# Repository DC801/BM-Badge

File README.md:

# DC801 Black Mage Badge

The DC801 Badge Platform for DC28+, featuring a [playable web build](https://dc801.github.io/BM-Badge/) to increase ease of access for content authorship workflows, as well as for archival access to the game when for the hardware is no longer available.

## Introducing Chapter 2 (for DC32)

A new expansion for the game has been added! Chapter 2 introduces King Gibson's castle and the badge's built-in USB-C serial interface. More characters, more puzzles, and more puns!

Use the terminal to engage with the world and solve puzzles:

Chapter 1 content is still available with this release, and both chapters are accessible from the main menu.

## Videos about the project

<a href="https://www.youtube.com/watch?v=QbsCsldlNKE" target="_blank">
<br />Watch Alex Chaveriat's review of the DC801 Black Mage Badge</a>

----

<a href="https://www.youtube.com/watch?v=-YtiRvzJ-uo" target="_blank">
<br />Watch Alex Chaveriat interview Hamster at DEFCON 29 about the DC801 Black Mage Badge</a>

----

<a href="https://www.youtube.com/watch?v=cmqgIxQA0Sg" target="_blank">
<br />Watch Alex Chaveriat interview Admiral Potato and Alamedyang about building the DC801 Black Mage Badge</a>

## Hardware

The DC801 BM-Badge brings you an expandable iteration of our robust platfom.

 - Core CPU is the Nordic nRF52840 SoC, on the u-blox BMD-340 module
   - [https://www.u-blox.com/en/product/bmd-34-series-open-cpu](https://www.u-blox.com/en/product/bmd-34-series-open-cpu)
   - 256k RAM, 1M internal flash, ARM® Cortex™ M4F CP @ 64Mhz
   - Bluetooth 5 with Bluetooth mesh and Zigbee support
   - Temperature sensor
 - 27 buttons with NKRO via a dedicated controller
   - Microchip ATiny1617 microcontroller, with UPDI programming support
   - [https://www.microchip.com/wwwproducts/en/ATtiny1617](https://www.microchip.com/wwwproducts/en/ATtiny1617)
 - 19 LEDs
 - SD card socket
 - 32MB of quad-spi flash
 - NAU8810 audio codec and speaker
 - 2.4" 240x320 TFT LCD screen with touch panel
 - LiPo battery with on-board charging
 - USB-C interface supporting USB endpoints
 - SAO 1.69bis and Saintcon MiniBadge expansion headers
 - Support for the DC801 ART front board expansion
 - JTAG via both standard ARM interface as well as Tag Connect
 - USB drag-and-drop programming via a UF2 interface (based on the [adafruit bootloader](https://github.com/adafruit/Adafruit_nRF52_Bootloader))
 - Exciting new artwork and sandwich design

Board design is in KiCad

See the [HW](/HW) directory for more info, schematics and etc

### ART - Asymmetric Resistive Token
Since this badge is a sandwich platform badge, we've include a template so that you can design your own front boards.

Check out the [Template](/HW/ART/Template) that you can create a new project in KiCad with.

## Software
 - Environment is GNU ARM GCC with your choice of IDE (We're currently using CLion and VSCode)
 - Need a J-Link Segger JTAG programmer to program the chip directly.
 - Custom game engine purpose-built for the badge that can automatically load custom games from the SD Card.
 - Included in the [SD_Card/MAGE](/SD_Card/MAGE) directory is a binary encoder that allows you to generate your own games with our engine using open source tools such as the Tiled Map Editor and our custom json scripting language.
 - Instructions to set up your own dev environment and desktop testing build of our game engine in [EnvironmentSetup.md](/EnvironmentSetup).
 - [Comprehensive engine documentation and content creation guide](SD_Card/MAGE/README.md)

## Gameplay Videos

[DC28 DC801 SAFEMODE badge, 2020-12-04 development update](https://vimeo.com/487527877): Watch almost 6 minutes of 100% in-engine gameplay in our 2020-12-04 development update video!

[DC28 DC801 SAFEMODE badge, 2021-02-21 development update](https://vimeo.com/515088170):
Watch one of our puzzles and see some of our new narrative focused engine scripting capabilities in our 2021-02-21 development update video!

----

## DC32 dev team

### Hardware

#### PCB Electronics
- @hamster

#### PCB Art
- corfidbizna
- alamedyang

#### Badge Design
- @admiral_potato
- @hamster

#### Art Board
- redactd

#### Joystick Covers
- @_Pexie

#### Software

#### Engine Lead
- @admiral_potato

#### Script System
- @admiral_potato

#### Script Tooling
- alamedyang
- @admiral_potato
- nibley

#### Programming Support
- Tawnos
- Solra Bizna
- Youssef Moosa
- Cedric Hutchings (cedric_h)

### Graphics

#### 2D Art
- alamedyang
- corfidbizna
- Hippi3Hack3r

#### 3D Art
- @admiral_potato
- nthday

### Story

#### Writing
- alamedyang
- Hippi3Hack3r

#### Scripting
- alamedyang
- ThatDeadGuy and CJDJ
- nibley
- mmedei
- korinakuma

#### Goose Facts Consultant
- lys

### Special Thanks
- 7thdrxn
- Aaron Freed
- anonbecause
- courtyen
- DisplayGFX
- flame3722
- HeyItsWaters
- hipu
- HumanDLC
- korinakuma
- laughdat
- Liam "junkmail" Thomas
- @MuxLuxx
- NewGnu
- @_Pexie
- Solra Bizna
- Spooks
- TuckleberryWinn
- And all the playtesters who we missed!

----

## DC28 dev team

Project owner
- [@nemus](https://twitter.com/Nemus801)

Software Team
- [@_bashNinja](https://twitter.com/_bashNinja)
- [@admiral_potato](https://twitter.com/admiral_potato)
- [@corfidbizna](https://twitter.com/corfidbizna)
- [kiyoshigawa](https://twa.ninja/)
- [@newzie1](https://twitter.com/newzie1)
- [@tazmodius](https://twitter.com/tazmodius)
- @alamedyang

Hardware Team
- [@dvdfreitag](https://twitter.com/dvdfreitag)
- [@hamster](https://twitter.com/hamster)

Honorable Mention
- [@pips801](https://twitter.com/pips801)

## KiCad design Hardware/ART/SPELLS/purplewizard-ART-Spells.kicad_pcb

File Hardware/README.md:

We will provide the hardware schematics and KiCAD files once we ship the final badge designs.

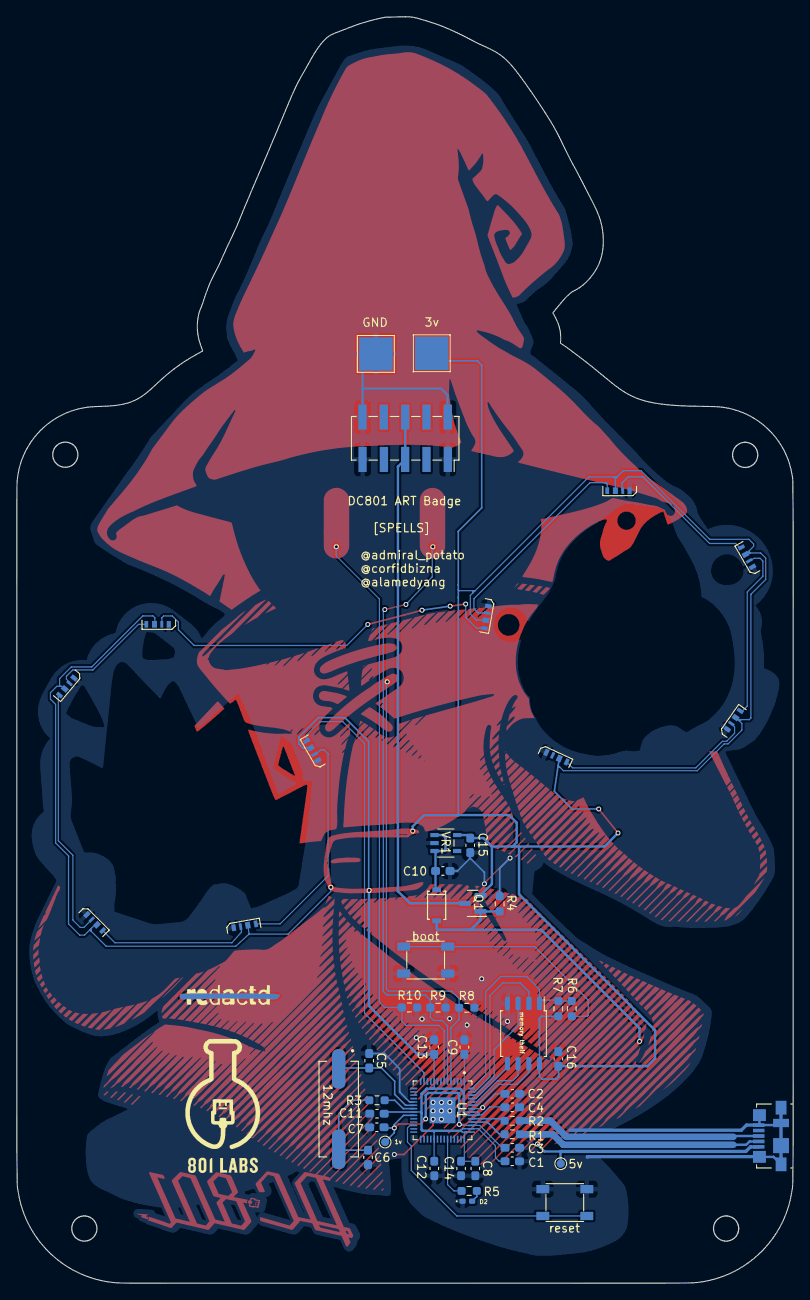
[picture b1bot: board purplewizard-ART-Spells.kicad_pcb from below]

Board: 2 copper layers, 92.5 x 151.0 mm, 52 parts (52 on the bottom side), 36 nets.

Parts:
1v: 1v; TestPoint_Pad_D1.0mm
3v: 3v3; TestPoint_Pad_4.0x4.0mm
5v: 5v; TestPoint_Pad_D1.0mm
12mhz: ABLS-12.000MHZ-B4-T; XTAL1140X470X420N
C1, C10, C15: 1uF; C_0603_1608Metric_Pad1.08x0.95mm_HandSolder
C2, C4, C7, C8, C9, C11, C12, C13, C14, C16: 100n; C_0603_1608Metric_Pad1.08x0.95mm_HandSolder
C3: 1u; C_0603_1608Metric_Pad1.08x0.95mm_HandSolder
C5, C6: 27pF; C_0603_1608Metric_Pad1.08x0.95mm_HandSolder
D1: D_Schottky; SM5819PL-TP
D2: LED; LED_0402_1005Metric_Pad0.77x0.64mm_HandSolder
D3, D4, D5, D6, D7, D8, D9, D10, D11, D12: LED_SK6812_4020_SIDE
GND: GND; TestPoint_Pad_4.0x4.0mm
J1: ART Expansion; PinSocket_2x05_P2.54mm_Vertical_SMD
J4: USB_B_Micro; USB_Micro-B_Molex_47346-0001
Q1: DMG2301L; SOT-23
R1, R2: 27; R_0603_1608Metric_Pad0.98x0.95mm_HandSolder
R3, R5, R6: 1k; R_0603_1608Metric_Pad0.98x0.95mm_HandSolder
R4, R7: 10k; R_0603_1608Metric_Pad0.98x0.95mm_HandSolder
R8, R9, R10: 1M; R_0603_1608Metric_Pad0.98x0.95mm_HandSolder
Ref**: Val**; redactd_copper_strike_v1
U1: RP2040; QFN40P700X700X90-57N
VR1: AP7366-33W5-7; AP7365-33WG-7
boot: SW_SPST; SW_SPST_PTS647
memory theif: W25Q32JVSS; SOIC-8_5.23x5.23mm_P1.27mm
reset: SW_SPST_PTS647

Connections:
+1V1: 1v.1, C2.1, C3.2, C7.1, U1.23 (DVDD), U1.45 (VREG_VOUT), U1.50 (DVDD)
+3.3VP: J1.5, J1.6, Q1.3 (D)
+3V3: 3v.1, C1.2, C4.1, C8.1, C9.1, C11.1, C12.1, C13.1, C14.1, C15.1, C16.1, D3.2 (VDD), D4.2 (VDD), D5.2 (VDD), D6.2 (VDD), D7.2 (VDD), D8.2 (VDD), D9.2 (VDD), D10.2 (VDD), D11.2 (VDD), D12.2 (VDD), Q1.2 (S), R7.1, U1.1 (IOVDD), U1.10 (IOVDD), U1.22 (IOVDD), U1.33 (IOVDD), U1.42 (IOVDD), U1.43 (ADC_AVDD), U1.44 (VREG_VIN), U1.48 (USB_VDD), U1.49 (IOVDD), VR1.5 (OUT), memory theif.8 (VCC)
D+: J4.3 (D+), R2.2
D-: J4.2 (D-), R1.2
GND: C1.1, C2.2, C3.1, C4.2, C5.1, C6.1, C7.2, C8.2, C9.2, C10.2, C11.2, C12.2, C13.2, C14.2, C15.2, C16.2, D2.1 (K), D3.4 (GND), D4.4 (GND), D5.4 (GND), D6.4 (GND), D7.4 (GND), D8.4 (GND), D9.4 (GND), D10.4 (GND), D11.4 (GND), D12.4 (GND), GND.1, J1.1, J1.2, J1.9, J1.10, J4.5 (GND), J4.6 (Shield), R4.2, R8.2, R9.2, R10.2, U1.19 (TESTEN), U1.57 (GND), VR1.2 (GND), boot.2 (B), memory theif.4 (GND), reset.2 (B)
GPIO25: R5.1, U1.37 (GPIO25)
NEO: D3.1 (DIN), U1.13 (GPIO10)
unnamed: 12mhz.2, C6.2, R3.2
unnamed: C10.1, D1.1 (K), VR1.1 (IN), VR1.3 (EN)
unnamed: D2.2 (A), R5.2
unnamed: D3.3 (DOUT), D4.1 (DIN)
unnamed: D4.3 (DOUT), D5.1 (DIN)
unnamed: D5.3 (DOUT), D6.1 (DIN)
unnamed: D6.3 (DOUT), D7.1 (DIN)
unnamed: D7.3 (DOUT), D8.1 (DIN)
unnamed: D8.3 (DOUT), D9.1 (DIN)
unnamed: D9.3 (DOUT), D10.1 (DIN)
unnamed: D10.3 (DOUT), D11.1 (DIN)
unnamed: D11.3 (DOUT), D12.1 (DIN)
unnamed: R1.1, U1.46 (USB_DM)
unnamed: R2.1, U1.47 (USB_DP)
QSPI_SCLK: U1.52 (QSPI_SCLK), memory theif.6 (CLK)
QSPI_SD0: U1.53 (QSPI_SD0), memory theif.5 (DI(IO0))
QSPI_SD1: U1.55 (QSPI_SD1), memory theif.2 (DO(IO1))
QSPI_SD2: U1.54 (QSPI_SD2), memory theif.3 (IO2)
QSPI_SD3: U1.51 (QSPI_SD3), memory theif.7 (IO3)
QSPI_SS: R6.1, R7.2, U1.56 (QSPI_CSN), memory theif.1 (~CS)
RUN: U1.26 (RUN), reset.1 (A)
TOUCH1: R8.1, U1.5 (GPIO3)
TOUCH2: R9.1, U1.6 (GPIO4)
TOUCH3: R10.1, U1.7 (GPIO5)
USB_BOOT: R6.2, boot.1 (A)
VBUS: 5v.1, D1.2 (A), J4.1 (VBUS), Q1.1 (G), R4.1
XIN: 12mhz.1, C5.2, U1.20 (XIN)
XOUT: R3.1, U1.21 (XOUT)

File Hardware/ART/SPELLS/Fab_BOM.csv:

,,,,,,,
,,,,,,,
,,,,,,,
,,Reference,Value,Package,Source,Datasheet,Quantity
,,"C2, C4, C7, C8, C9, C11, C12, C13, C14, C16",100n,0603,~,,10
,,"C1, C3, C10, C15",1u,0603,~,,4
,,"C5, C6",1pF,0603,~,,2
,,"R8, R9, R10",1M,0603,~,,3
,,"R1, R2",27,0603,~,,2
,,"R4, R7",10k,0603,~,,2
,,"R3, R5, R6",1k,0603,~,,3
,,"D3, D4, D5, D6, D7, D8, D9, D10, D11, D12",SK6812SIDE-A,,https://www.lcsc.com/product-detail/Light-Emitting-Diodes-LE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,~,10
,,D1,Schottky,SOD-123,https://www.digikey.com/en/products/detail/micro-commercial-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,,1
,,D2,Red,0402,https://www.lcsc.com/product-detail/Light-Emitting-Diodes-sp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,,1
,,Q1,DMG2301L,SOT-23,https://www.digikey.com/en/products/detail/diodes-incorporat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,,1
,,U1,RP2040,QFN56,https://www.lcsc.com/product-detail/Microcontroller-Units-MC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,,1
,,U2,W25Q32JVSS,SOIC-8,https://www.lcsc.com/product-detail/NOR-FLASH_Winbond-Elec-W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,,1
,,Y1,ABLS-12.000MHZ-B4-T,,https://www.digikey.com/en/products/detail/abracon-llc/ABLS-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,~,1
,,"SW1, SW2",SPST,,https://www.lcsc.com/product-detail/Tactile-Switches_TE-Conn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,,2
,,J1,2x5 2.54 SMD,,https://www.digikey.com/en/products/detail/amphenol-cs-fci/1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,,1
,,J4,USB Micro Molex,,https://www.digikey.com/en/products/detail/molex/0473460001/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,,1
,,VR1,AP7366-33W5-7,SOT-25,https://www.lcsc.com/product-detail/Linear-Voltage-Regulator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,~,1

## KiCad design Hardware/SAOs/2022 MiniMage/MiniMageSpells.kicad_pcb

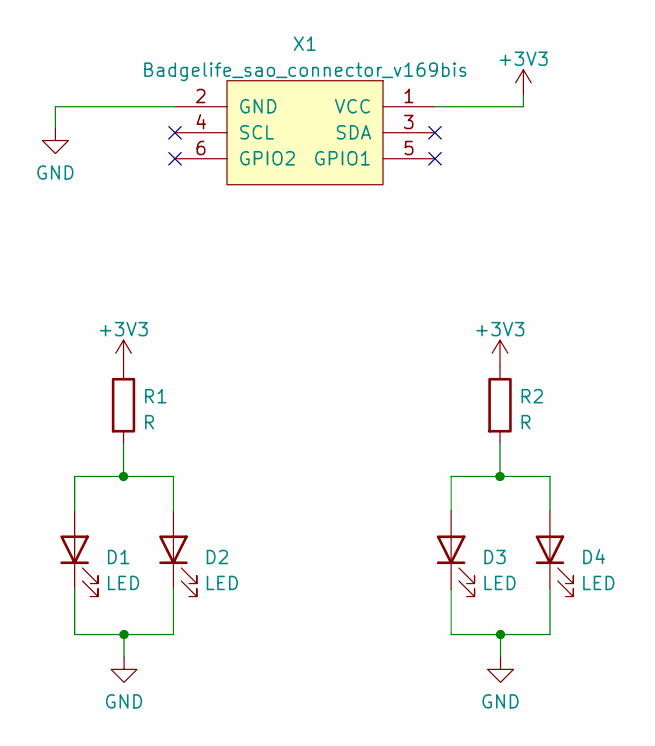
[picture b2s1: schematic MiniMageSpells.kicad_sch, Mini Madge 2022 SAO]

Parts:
D1, D2, D3, D4: LED; LED_0805_2012Metric
R1, R2: R; R_0805_2012Metric
X1: Badgelife_sao_connector_v169bis; PinHeader_2x03_P2.54mm_Vertical_SMD

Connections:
+3V3: R1.1, R2.1, X1.1 (VCC)
GND: D1.1 (K), D2.1 (K), D3.1 (K), D4.1 (K), X1.2 (GND)
unnamed: D1.2 (A), D2.2 (A), R1.2
unnamed: D3.2 (A), D4.2 (A), R2.2

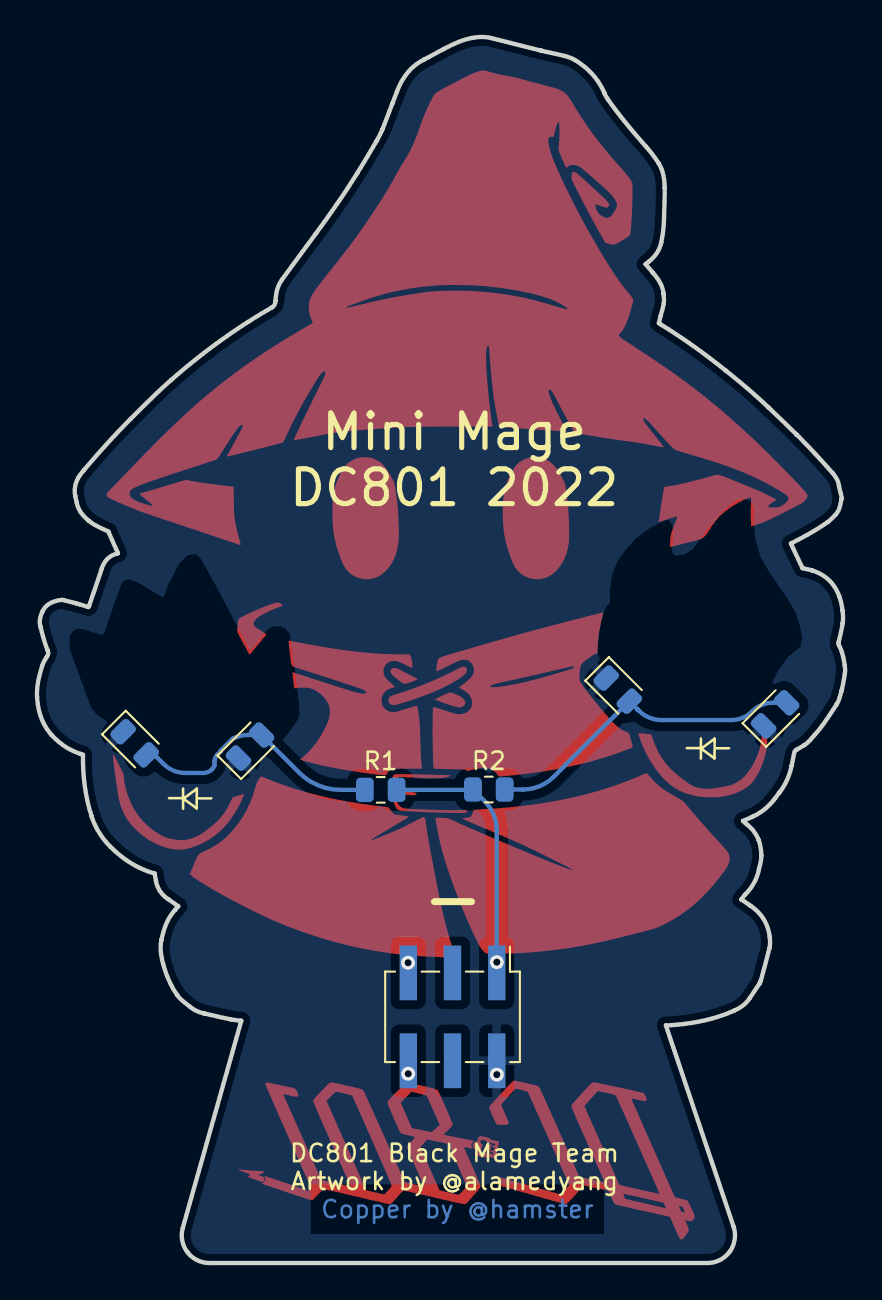
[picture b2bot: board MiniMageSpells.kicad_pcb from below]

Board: 2 copper layers, 46.4 x 70.4 mm, 7 parts (7 on the bottom side), 4 nets.

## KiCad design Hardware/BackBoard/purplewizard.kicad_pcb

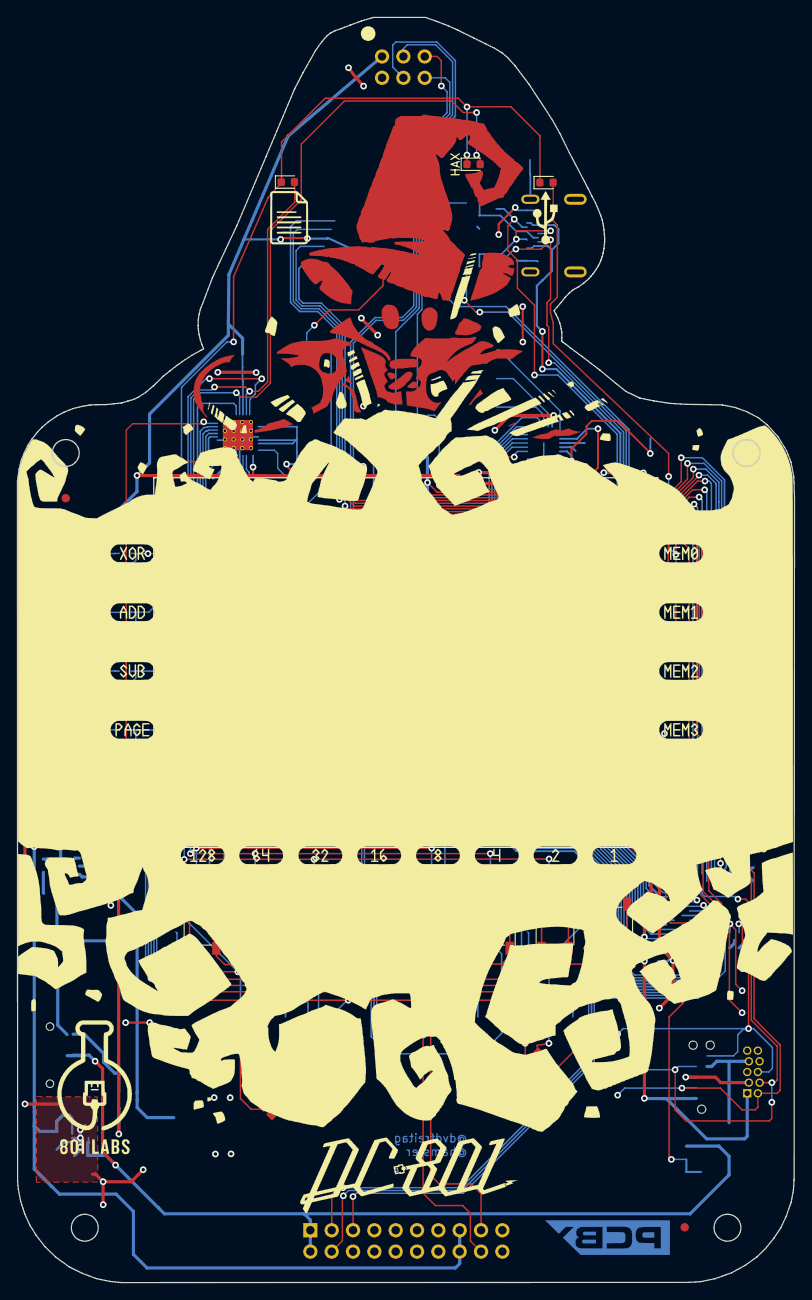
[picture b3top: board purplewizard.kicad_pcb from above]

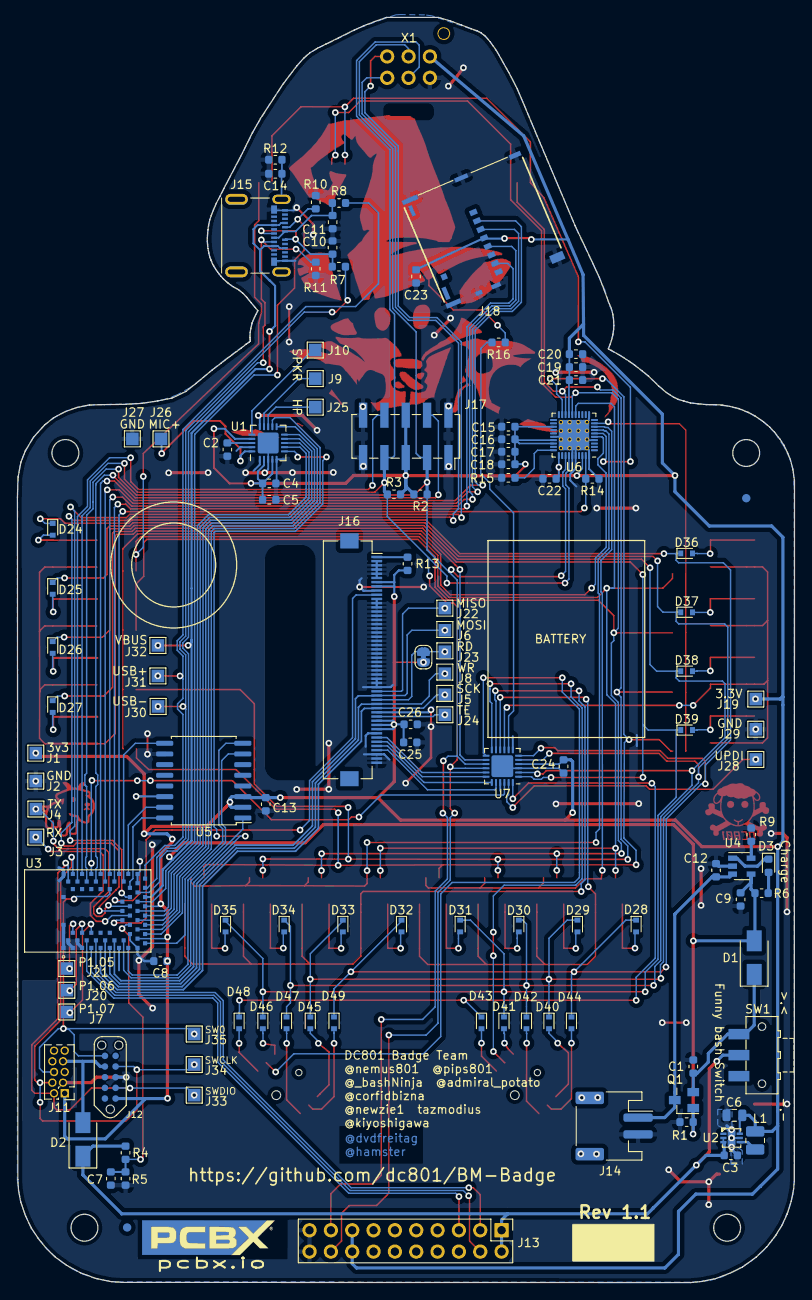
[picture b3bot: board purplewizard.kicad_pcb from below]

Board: 2 copper layers, 92.5 x 150.6 mm, 159 parts (118 on the bottom side), 121 nets.

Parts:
C1, C13, C14, C15, C17, C20, C23, C24, C25: 0.1uF; C_0603_1608Metric
C2, C4, C5, C8, C9, C12: 4.7uF; C_0603_1608Metric
C3, C26: 10uF; C_0603_1608Metric
C6: 22uF; C_0805_2012Metric
C7: 1nF; C_0603_1608Metric
C10, C11: 47pF; C_0603_1608Metric
C16, C18, C21, C22: 0.47uF; C_0603_1608Metric
C19: 22uF; C_0603_1608Metric
D1, D2: D_Schottky; D_SMA
D3: RED; LED_0603_1608Metric
D5: XOR; LED_0603_1608Metric
D6: MEM0; LED_0603_1608Metric
D7: BIT128; LED_0603_1608Metric
D8: BIT8; LED_0603_1608Metric
D9: USB; LED_0603_1608Metric
D10: ADD; LED_0603_1608Metric
D11: MEM1; LED_0603_1608Metric
D12: BIT64; LED_0603_1608Metric
D13: BIT4; LED_0603_1608Metric
D14: HAX; LED_0603_1608Metric
D15: SUB; LED_0603_1608Metric
D16: MEM2; LED_0603_1608Metric
D17: BIT32; LED_0603_1608Metric
D18: BIT2; LED_0603_1608Metric
D19: SD; LED_0603_1608Metric
D20: PAGE; LED_0603_1608Metric
D21: MEM3; LED_0603_1608Metric
D22: BIT16; LED_0603_1608Metric
D23: BIT1; LED_0603_1608Metric
D24, D25, D26, D27, D28, D29, D30, D31, D32, D33, D34, D35, D36, D37, D38, D39, D40, D41, D42, D43, D44, D45, D46, D47, D48, D49: D_ALT; D_SOD-523
FID1, FID2, FID3, FID4: Fiducial; Fiducial_1mm_Mask2mm
J1, J19: 3.3V; TestPoint_Pad_1.5x1.5mm
J2, J27, J29: GND; TestPoint_Pad_1.5x1.5mm
J3: UART_TX; TestPoint_Pad_1.5x1.5mm
J4: UART_RX; TestPoint_Pad_1.5x1.5mm
J5: LCD_SCK; TestPoint_Pad_1.5x1.5mm
J6: LCD_MOSI; TestPoint_Pad_1.5x1.5mm
J7: P1.07; TestPoint_Pad_1.5x1.5mm
J8: LCD_WR; TestPoint_Pad_1.5x1.5mm
J9: SPKR+; TestPoint_Pad_1.5x1.5mm
J10: SPKR-; TestPoint_Pad_1.5x1.5mm
J11: JTAG; PinHeader_2x05_P1.27mm_Vertical_Sneaky
J12: TagConnect; TC2050-NL_SMALL
J13: Minibadge Expansion; PinSocket_2x10_P2.54mm_Vertical
J14: Battery; JST_PH_S2B-PH-SM4-TB_1x02-1MP_P2.00mm_Horizontal
J15: USB_C_Receptacle_USB2.0; MOLEX_105450-0101
J16: Conn_01x50; Hirose_FH12-50S-0.5SH_1x50-1MP_P0.50mm_Horizontal
J17: Board to Board; PinSocket_2x05_P2.54mm_Vertical_SMD
J18: Micro_SD_Card; JAE_ST11S008V4HR2000
J20: P1.06; TestPoint_Pad_1.5x1.5mm
J21: P1.05; TestPoint_Pad_1.5x1.5mm
J22: LCD_MISO; TestPoint_Pad_1.5x1.5mm
J23: LCD_RD; TestPoint_Pad_1.5x1.5mm
J24: LCD_TE; TestPoint_Pad_1.5x1.5mm
J25: MOUT; TestPoint_Pad_1.5x1.5mm
J26: MIC+; TestPoint_Pad_1.5x1.5mm
J28: UPDI; TestPoint_Pad_1.5x1.5mm
J30: USB-; TestPoint_Pad_1.5x1.5mm
J31: USB+; TestPoint_Pad_1.5x1.5mm
J32: VBUS; TestPoint_Pad_1.5x1.5mm
J33: SWDIO; TestPoint_Pad_1.5x1.5mm
J34: SWCLK; TestPoint_Pad_1.5x1.5mm
J35: SWO; TestPoint_Pad_1.5x1.5mm
JP1: SolderJumper_2_Bridged; SolderJumper-2_P1.3mm_Bridged_RoundedPad1.0x1.5mm
L1: 1uH; L_1008_2520Metric
Q1: AO3409; SuperSOT-3
R1, R12: 10k; R_0603_1608Metric
R2, R3: 4.7k; R_0603_1608Metric
R4: 806k; R_0603_1608Metric
R5: 2M; R_0603_1608Metric
R6: 470R; R_0603_1608Metric
R7, R8: 27R; R_0603_1608Metric
R9: 2.0k; R_0603_1608Metric
R10, R11: 5.1k; R_0603_1608Metric
R13: 33R; R_0603_1608Metric
R14: 100k; R_0603_1608Metric
R15: 20k; R_0603_1608Metric
R16: 1k; R_0603_1608Metric
SW1: Power; SW_SPDT_CK-JS102011SAQN
SW2, SW3, SW4, SW5, SW6, SW7, SW8, SW9, SW10, SW11, SW12, SW13, SW14, SW15, SW16, SW17: TACTILE; SW_SPST_PTS647
SW18, SW19: SKRHABE010
U1: NAU8810; QFN-20-1EP_4x4mm_P0.5mm_EP2.5x2.5mm
U2: SC189ZULTRT
U3: BMD-340; RIGADO_BMD-340
U4: MCP73832-2-OT; SOT-23-5
U5: S25FL256S; SOIC-16W_7.5x10.3mm_P1.27mm
U6: IS31FL3736; QFN-40-1EP_5x5mm_P0.4mm_EP3.6x3.6mm_LargerThermalVias
U7: ATtiny1617-M; QFN-24-1EP_4x4mm_P0.5mm_EP2.6x2.6mm
X1: Badgelife_sao_connector_v169bis; Badgelife-Shitty-v1.69bis

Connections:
+3V3: C4.2, C5.2, C6.1, C8.1, C13.2, C15.1, C16.2, C17.1, C18.2, C19.1, C20.1, C21.2, C22.1, C23.2, C24.2, C25.2, C26.2, J1.1, J11.1, J12.1, J13.15, J13.16, J16.7, J16.8, J16.40, J16.41, J16.42, J17.5, J17.6, J18.4 (VDD), J19.1, JP1.2 (B), L1.2, R2.2, R3.2, R13.1, U1.2 (VDDA), U1.4 (VDDD), U1.17 (VDDSPK), U2.6 (OUT), U3.17 (Vcc), U3.65 (Vcch1), U5.2 (Vcc), U5.3 (~Reset), U5.14 (VIO), U6.17 (PVCC), U6.23 (PVCC), U6.27 (DVCC), U6.28 (AVCC), U6.31 (VIO), U6.38 (SDB), U7.4 (VCC), X1.1 (VCC)
+BATT: C12.2, J14.1, Q1.3 (D), U4.3 (Vbat)
+BATT_SW: C3.1, D2.1 (K), J13.1, J13.2, R4.2, SW1.2 (B), U2.2 (EN), U2.3 (Vin)
C0: SW2.2 (B), SW3.2 (B), SW4.2 (B), SW5.2 (B), U7.14 (PB2)
C1: SW6.2 (B), SW7.2 (B), SW8.2 (B), SW9.2 (B), U7.10 (PB6)
C2: SW10.2 (B), SW11.2 (B), SW12.2 (B), SW13.2 (B), U7.11 (PB5)
C3: SW14.2 (B), SW15.2 (B), SW16.2 (B), SW17.2 (B), U7.9 (PB7)
C4: SW18.5 (Common), U7.12 (PB4)
C5: SW19.5 (Common), U7.13 (PB3)
EXP1: J17.4, U3.38 (P0.20)
EXP2: J17.8, U3.42 (P0.24)
GND: C1.2, C2.1, C3.2, C4.1, C5.1, C6.2, C7.2, C8.2, C9.1, C10.1, C11.2, C12.1, C13.1, C14.2, C15.2, C16.1, C17.2, C18.1, C19.2, C20.2, C21.1, C22.2, C23.1, C24.1, C25.1, C26.1, J2.1, J11.3, J12.3, J13.19, J13.20, J14.2, J15.A1 (GND), J15.A12 (GND), J15.B1 (GND), J15.B12 (GND), J16.2, J16.3, J16.4, J16.5, J16.6, J16.9, J16.11, J16.12, J16.13, J16.14, J16.15, J16.16, J16.17, J16.18, J16.19, J16.20, J16.21, J16.22, J16.23, J16.24, J16.25, J16.26, J16.27, J16.28, J16.29, J16.30, J16.31, J16.32, J16.38, J16.43, J16.48, J16.49, J16.50, J17.1, J17.2, J17.9, J17.10, J18.6 (VSS), J18.9 (GND@1), J18.10 (GND@2), J18.11 (GND@3), J18.15 (GND@4), J18.16 (GND@5), J18.17 (GND@6), J18.18 (GND@7), J27.1, J29.1, R1.1, R5.1, R9.1, R10.2, R11.1, R12.2, R14.1, R15.1, U1.3 (VSSA), U1.5 (VSSD), U1.15 (VSSSPK), U2.5 (GND), U2.EP, U3.1 (GND1), U3.2 (GND1), U3.3 (GND1), U3.4 (GND1), U3.5 (GND1), U3.16 (GND1), U3.18 (GND1), U3.29 (GND1), U3.30 (GND1), U3.45 (GND1), U3.46 (GND1), U3.47 (GND1), U3.55 (GND1), U4.2 (Vss), U5.10 (Vss), U6.4 (PGND), U6.11 (PGND), U6.26 (AGND), U6.35 (ADDR1), U6.36 (ADDR2), U6.40 (GND), U6.41 (TGND), U7.3 (GND), U7.25 (GND), X1.2 (GND)
I2S_LRCK: U1.8 (LRCK), U3.64 (P1.15)
I2S_MCK: U1.10 (MCK), U3.63 (P1.14)
I2S_SCK: U1.9 (SCK), U3.21 (P0.05/AIN3)
I2S_SCL: U1.11 (SCL), U3.19 (P0.03/AIN1)
I2S_SDA: U1.12 (SDA), U3.62 (P1.13)
I2S_SDIN: U1.6 (SDOUT), U3.12 (P0.31)
I2S_SDOUT: U1.7 (SDIN), U3.23 (P0.07)
KEY_INT: U3.39 (P0.18), U7.22 (PC5)
LC0: D5.2 (A), D6.2 (A), D7.2 (A), D8.2 (A), D9.2 (A), U6.15 (CS1)
LC1: D10.2 (A), D11.2 (A), D12.2 (A), D13.2 (A), D14.2 (A), U6.16 (CS2)
LC2: D15.2 (A), D16.2 (A), D17.2 (A), D18.2 (A), D19.2 (A), U6.18 (CS3)
LC3: D20.2 (A), D21.2 (A), D22.2 (A), D23.2 (A), U6.19 (CS4)
LCD_MISO: J16.33, J22.1
LCD_MOSI: J6.1, J16.34, U3.11 (P0.30)
LCD_RD: J16.35, J23.1, JP1.1 (A)
LCD_RESET: J16.10, U3.53 (P1.10)
LCD_SCK: J5.1, J16.37, U3.9 (P0.28)
LCD_TE: J16.39, J24.1
LCD_WR: J8.1, J16.36, U3.10 (P0.29)
LED_RESET: R14.2, U3.33 (P0.15/TRACEDATA[2]), U6.39 (IICRST)
LR0: D5.1 (K), D10.1 (K), D15.1 (K), D20.1 (K), U6.9 (SW8)
LR1: D6.1 (K), D11.1 (K), D16.1 (K), D21.1 (K), U6.5 (SW4)
LR2: D7.1 (K), D12.1 (K), D17.1 (K), D22.1 (K), U6.8 (SW7)
LR3: D8.1 (K), D13.1 (K), D18.1 (K), D23.1 (K), U6.7 (SW6)
LR4: D9.1 (K), D14.1 (K), D19.1 (K), U6.6 (SW5)
MB_MISO: J13.4, U3.7 (P0.26)
MB_MOSI: J13.3, U3.8 (P0.27)
MB_SCK: J13.5, U3.6 (P0.25)
MEM_CS: U3.15 (P0.02/AIN0), U5.7 (~CS)
MEM_IO0: U3.31 (P0.13), U5.15 (IO0)
MEM_IO1: U3.61 (P1.12), U5.8 (IO1)
MEM_IO2: U3.32 (P0.14), U5.9 (IO2)
MEM_IO3: U3.14 (P0.01/XTAL2), U5.1 (IO3)
MEM_SCK: U3.28 (P0.12), U5.16 (SCK)
unnamed: C1.1, D1.1 (K), Q1.2 (S), SW1.3 (C)
unnamed: C2.2, U1.18 (VREF)
unnamed: C10.2, J15.A7 (D-), J15.B7 (D-), R7.1
unnamed: C11.1, J15.A6 (D+), J15.B6 (D+), R8.1
unnamed: C14.1, J15.S1 (SHIELD), R12.1
unnamed: D3.1 (K), U4.1 (STAT)
unnamed: D3.2 (A), R6.2
unnamed: J7.1, U3.50 (P1.07)
unnamed: J9.1, U1.14 (SPKOUT+)
unnamed: J10.1, U1.16 (SPKOUT-)
unnamed: J16.1, R13.2
unnamed: J20.1, U3.49 (P1.06)
unnamed: J21.1, U3.48 (P1.05)
unnamed: J25.1, U1.13 (MOUT)
unnamed: J26.1, U1.20 (MIC+)
unnamed: L1.1, U2.4 (LX)
unnamed: R9.2, U4.5 (PROG)
unnamed: R15.2, U6.30 (RSET)
unnamed: R16.2, U7.8 (PA7)
unnamed: D24.2 (A), SW2.1 (A)
unnamed: D25.2 (A), SW3.1 (A)
unnamed: D26.2 (A), SW4.1 (A)
unnamed: D27.2 (A), SW5.1 (A)
unnamed: D28.2 (A), SW6.1 (A)
unnamed: D29.2 (A), SW7.1 (A)
unnamed: D30.2 (A), SW8.1 (A)
unnamed: D31.2 (A), SW9.1 (A)
unnamed: D32.2 (A), SW10.1 (A)
unnamed: D33.2 (A), SW11.1 (A)
unnamed: D34.2 (A), SW12.1 (A)
unnamed: D35.2 (A), SW13.1 (A)
unnamed: D36.2 (A), SW14.1 (A)
unnamed: D37.2 (A), SW15.1 (A)
unnamed: D38.2 (A), SW16.1 (A)
unnamed: D39.2 (A), SW17.1 (A)
unnamed: D40.2 (A), SW18.1 (A)
unnamed: D44.2 (A), SW18.2 (Center)
unnamed: D42.2 (A), SW18.3 (C)
unnamed: D41.2 (A), SW18.4 (B)
unnamed: D43.2 (A), SW18.6 (D)
unnamed: D45.2 (A), SW19.1 (A)
unnamed: D49.2 (A), SW19.2 (Center)
unnamed: D47.2 (A), SW19.3 (C)
unnamed: D46.2 (A), SW19.4 (B)
unnamed: D48.2 (A), SW19.6 (D)
R0: D24.1 (K), D28.1 (K), D32.1 (K), D36.1 (K), D44.1 (K), D49.1 (K), U7.6 (PA5)
R1: D25.1 (K), D29.1 (K), D33.1 (K), D37.1 (K), D40.1 (K), D45.1 (K), U7.5 (PA4)
R2: D26.1 (K), D30.1 (K), D34.1 (K), D38.1 (K), D42.1 (K), D47.1 (K), U7.2 (PA3)
R3: D27.1 (K), D31.1 (K), D35.1 (K), D39.1 (K), D41.1 (K), D46.1 (K), U7.1 (PA2)
R4: D43.1 (K), D48.1 (K), U7.24 (PA1)
S1_1: U3.26 (P0.10/NFC2), X1.5 (GPIO1)
S1_2: U3.54 (P1.11), X1.6 (GPIO2)
SCL: J13.18, J17.7, R3.1, U3.41 (P0.23), U6.34 (SCL), U7.16 (PB0), X1.4 (SCL)
SDA: J13.17, J17.3, R2.1, U3.40 (P0.22), U6.33 (SDA), U7.15 (PB1), X1.3 (SDA)
SD_CS: J18.2 (DAT3/CD), U3.37 (P0.19)
SD_MISO: J18.7 (DAT0), U3.34 (P0.16/TRACEDATA[1])
SD_MOSI: J18.3 (CMD), U3.36 (P0.21)
SD_SCK: J18.5 (CLK), U3.35 (P0.17)
SW0: J11.6, J12.6, J35.1, U3.56 (TRACEDATA[0]/SW0/P1.00)
SWCLK: J11.4, J12.4, J34.1, U3.43 (SWCLK)
SWDIO: J11.2, J12.2, J33.1, U3.44 (SWDIO)
TC_PWR: D2.2 (A), J11.7, J12.7
TOUCH_X+: J16.44, U7.17 (PC0)
TOUCH_X-: J16.46, U7.19 (PC2)
TOUCH_Y+: J16.45, U7.18 (PC1)
TOUCH_Y-: J16.47, U7.20 (PC3)
UART_RX: J4.1, U3.24 (P0.08)
UART_TX: J3.1, U3.22 (P0.06)
UPDI: J28.1, U7.23 (~RESET/PA0)
USB+: J31.1, R8.2, U3.68 (USB_D+)
USB-: J30.1, R7.2, U3.67 (USB_D-)
USB_CC1: J15.A5 (CC1), R10.1, U3.25 (P0.09/NFC1)
USB_CC2: J15.B5 (CC2), R11.2, U3.27 (P0.11)
VBAT_SENSE: C7.1, R4.1, R5.2, U3.20 (P0.04/AIN2)
VBUS: C9.2, D1.2 (A), J15.A4 (VBUS), J15.A9 (VBUS), J15.B4 (VBUS), J15.B9 (VBUS), J32.1, Q1.1 (G), R1.2, R6.1, U3.66 (Vbus), U4.4 (Vin)

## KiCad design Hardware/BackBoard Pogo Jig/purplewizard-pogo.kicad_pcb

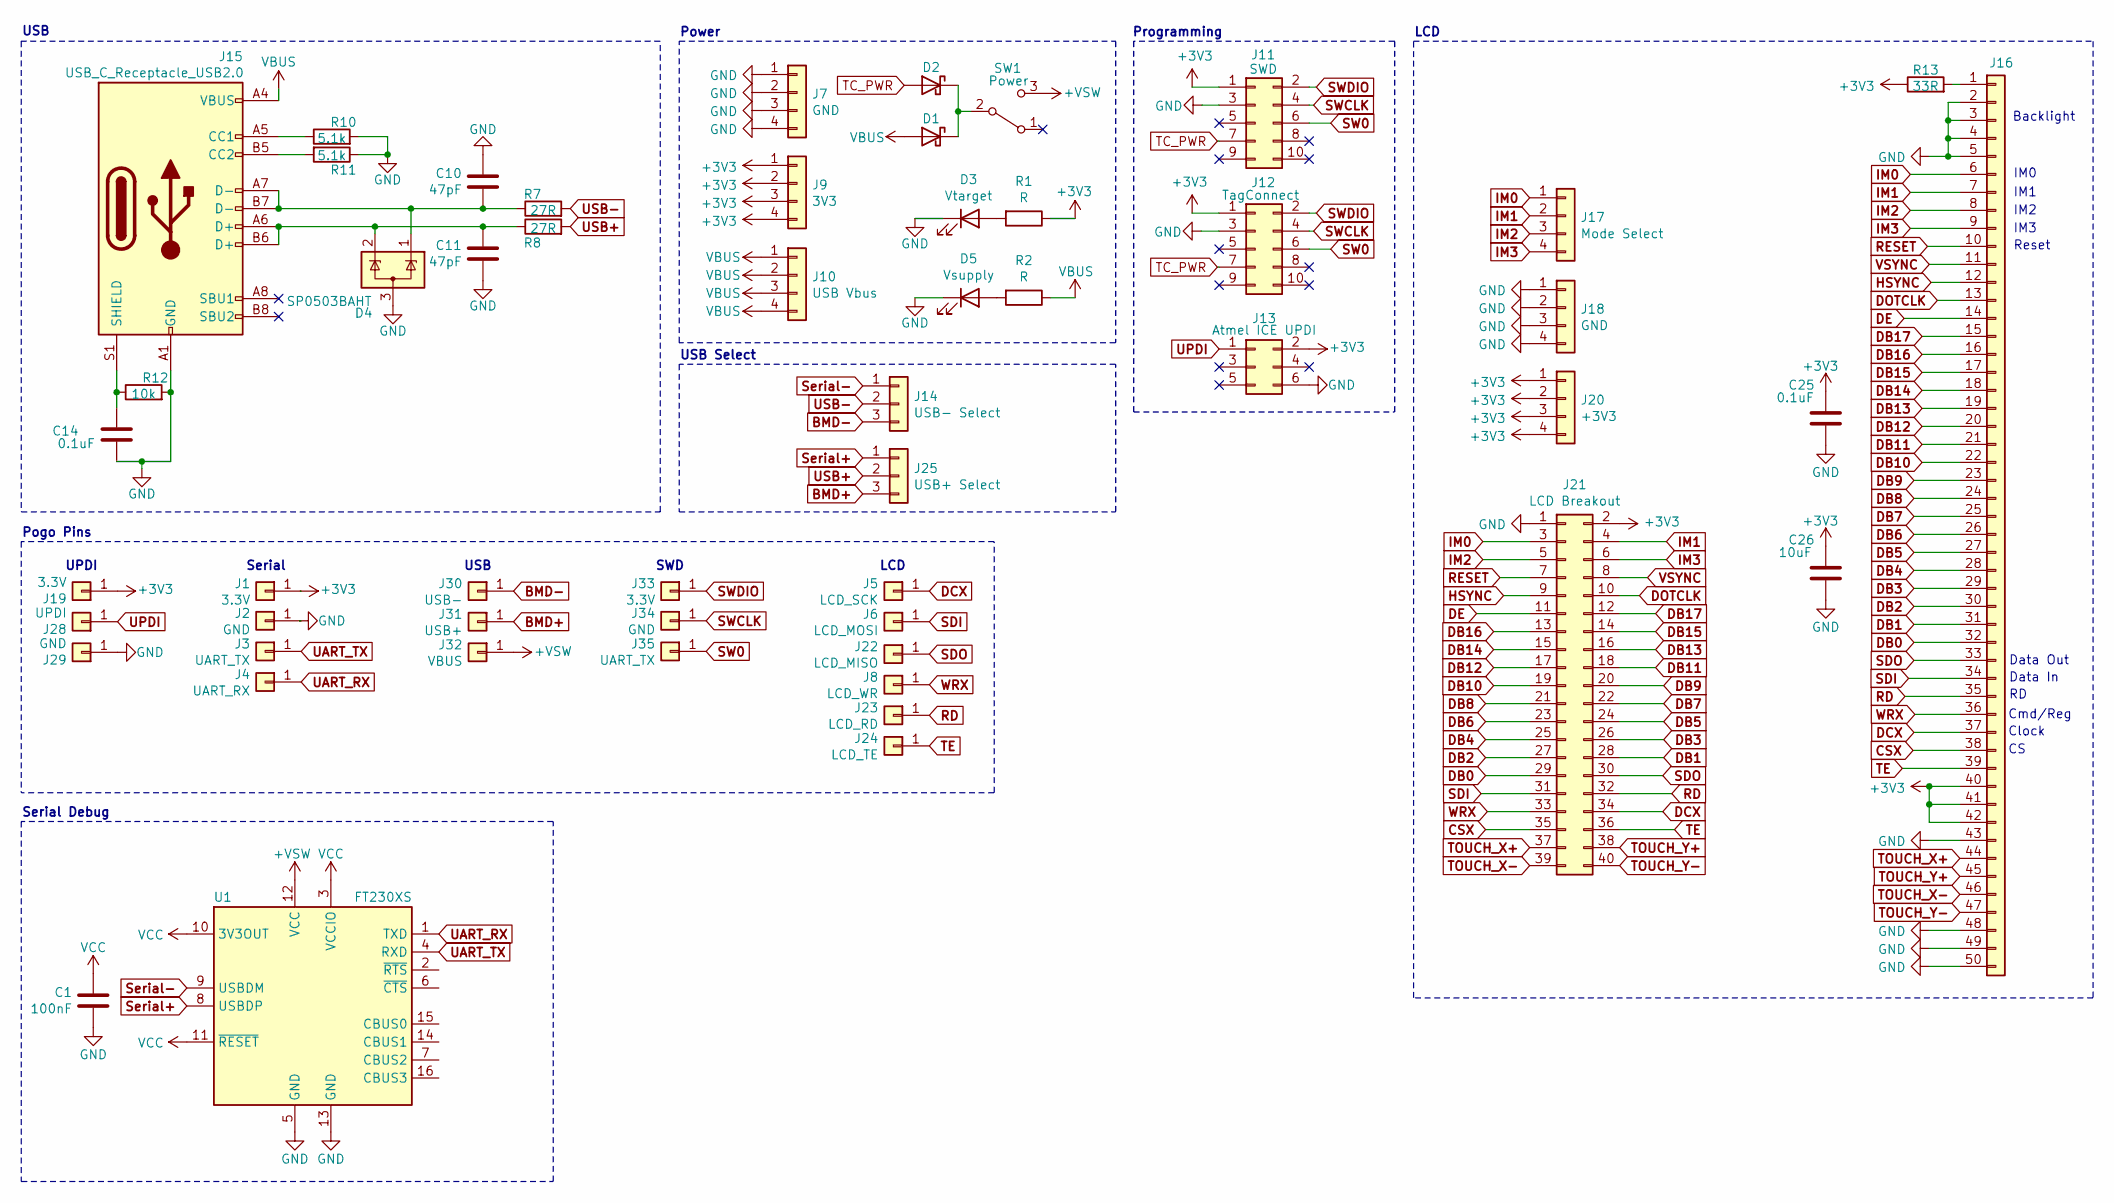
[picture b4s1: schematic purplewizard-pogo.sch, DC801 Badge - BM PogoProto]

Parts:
C1: 100nF; C_0603_1608Metric
C10, C11: 47pF; C_0603_1608Metric
C14, C25: 0.1uF; C_0603_1608Metric
C26: 10uF; C_0603_1608Metric
D1, D2: D_Schottky; D_SMA
D3: Vtarget; LED_0603_1608Metric
D4: SP0503BAHT; SOT-143
D5: Vsupply; LED_0603_1608Metric
J1, J19, J33: 3.3V; PogoSocket
J2, J29, J34: GND; PogoSocket
J3, J35: UART_TX; PogoSocket
J4: UART_RX; PogoSocket
J5: LCD_SCK; PogoSocket
J6: LCD_MOSI; PogoSocket
J7, J18: GND; PinHeader_1x04_P2.54mm_Vertical
J8: LCD_WR; PogoSocket
J9: 3V3; PinHeader_1x04_P2.54mm_Vertical
J10: USB Vbus; PinHeader_1x04_P2.54mm_Vertical
J11: SWD; PinHeader_2x05_P1.27mm_Vertical_Sneaky
J12: TagConnect; TC2050-NL_SMALL
J13: Atmel ICE UPDI; PinHeader_2x03_P2.54mm_Vertical
J14: USB- Select; PinHeader_1x03_P2.54mm_Vertical
J15: USB_C_Receptacle_USB2.0; MOLEX_105450-0101
J16: Conn_01x50; Hirose_FH12-50S-0.5SH_1x50-1MP_P0.50mm_Horizontal
J17: Mode Select; PinHeader_1x04_P2.54mm_Vertical
J20: +3V3; PinHeader_1x04_P2.54mm_Vertical
J21: LCD Breakout; PinHeader_2x20_P2.54mm_Vertical
J22: LCD_MISO; PogoSocket
J23: LCD_RD; PogoSocket
J24: LCD_TE; PogoSocket
J25: USB+ Select; PinHeader_1x03_P2.54mm_Vertical
J28: UPDI; PogoSocket
J30: USB-; PogoSocket
J31: USB+; PogoSocket
J32: VBUS; PogoSocket
R1, R2: R; R_0603_1608Metric
R7, R8: 27R; R_0603_1608Metric
R10, R11: 5.1k; R_0603_1608Metric
R12: 10k; R_0603_1608Metric
R13: 33R; R_0603_1608Metric
SW1: Power; SW_SPDT_CK-JS102011SAQN
U1: FT230XS; SSOP-16_3.9x4.9mm_P0.635mm

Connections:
+3V3: C25.2, C26.2, J1.1, J9.1, J9.2, J9.3, J9.4, J11.1, J12.1, J13.2, J16.40, J16.41, J16.42, J19.1, J20.1, J20.2, J20.3, J20.4, J21.2, R1.1, R13.1
+VSW: J32.1, SW1.3 (C), U1.12 (VCC)
BMD+: J25.3, J31.1
BMD-: J14.3, J30.1
CSX: J16.38, J21.35
DB0: J16.32, J21.29
DB1: J16.31, J21.28
DB2: J16.30, J21.27
DB3: J16.29, J21.26
DB4: J16.28, J21.25
DB5: J16.27, J21.24
DB6: J16.26, J21.23
DB7: J16.25, J21.22
DB8: J16.24, J21.21
DB9: J16.23, J21.20
DB10: J16.22, J21.19
DB11: J16.21, J21.18
DB12: J16.20, J21.17
DB13: J16.19, J21.16
DB14: J16.18, J21.15
DB15: J16.17, J21.14
DB16: J16.16, J21.13
DB17: J16.15, J21.12
DCX: J5.1, J16.37, J21.34
DE: J16.14, J21.11
DOTCLK: J16.13, J21.10
GND: C1.2, C10.1, C11.2, C14.2, C25.1, C26.1, D3.1 (K), D4.3 (A), D5.1 (K), J2.1, J7.1, J7.2, J7.3, J7.4, J11.3, J12.3, J13.6, J15.A1 (GND), J15.A12 (GND), J15.B1 (GND), J15.B12 (GND), J16.2, J16.3, J16.4, J16.5, J16.43, J16.48, J16.49, J16.50, J18.1, J18.2, J18.3, J18.4, J21.1, J29.1, R10.2, R11.1, R12.2, U1.5 (GND), U1.13 (GND)
HSYNC: J16.12, J21.9
IM0: J16.6, J17.1, J21.3
IM1: J16.7, J17.2, J21.4
IM2: J16.8, J17.3, J21.5
IM3: J16.9, J17.4, J21.6
unnamed: C10.2, D4.1 (K), J15.A7 (D-), J15.B7 (D-), R7.1
unnamed: C11.1, D4.2 (K), J15.A6 (D+), J15.B6 (D+), R8.1
unnamed: C14.1, J15.S1 (SHIELD), R12.1
unnamed: D1.1 (K), D2.1 (K), SW1.2 (B)
unnamed: D3.2 (A), R1.2
unnamed: D5.2 (A), R2.2
unnamed: J15.A5 (CC1), R10.1
unnamed: J15.B5 (CC2), R11.2
unnamed: J16.1, R13.2
RD: J16.35, J21.32, J23.1
RESET: J16.10, J21.7
SDI: J6.1, J16.34, J21.31
SDO: J16.33, J21.30, J22.1
SW0: J11.6, J12.6, J35.1
SWCLK: J11.4, J12.4, J34.1
SWDIO: J11.2, J12.2, J33.1
Serial+: J25.1, U1.8 (USBDP)
Serial-: J14.1, U1.9 (USBDM)
TC_PWR: D2.2 (A), J11.7, J12.7
TE: J16.39, J21.36, J24.1
TOUCH_X+: J16.44, J21.37
TOUCH_X-: J16.46, J21.39
TOUCH_Y+: J16.45, J21.38
TOUCH_Y-: J16.47, J21.40
UART_RX: J4.1, U1.1 (TXD)
UART_TX: J3.1, U1.4 (RXD)
UPDI: J13.1, J28.1
USB+: J25.2, R8.2
USB-: J14.2, R7.2
VBUS: D1.2 (A), J10.1, J10.2, J10.3, J10.4, J15.A4 (VBUS), J15.A9 (VBUS), J15.B4 (VBUS), J15.B9 (VBUS), R2.1
VCC: C1.1, U1.3 (VCCIO), U1.10 (3V3OUT), U1.11 (~RESET)
VSYNC: J16.11, J21.8
WRX: J8.1, J16.36, J21.33

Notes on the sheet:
Programming
Reset
Data In
Cmd/Reg
Clock
IM0
IM1
IM2
IM3
Data Out
LCD
Backlight
Pogo Pins
UPDI
Serial
USB
SWD
Power
Serial Debug
USB Select

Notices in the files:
parts and their libraries:
Copyright 2016 Accelerated Designs. All rights reserved.
